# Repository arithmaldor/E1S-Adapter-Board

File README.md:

# Copyright and Disclaimer
Copyright: Jacob Proctor 2018

This documentation describes Open Hardware and is licensed under the
CERN OHL v. 1.2.

You may redistribute and modify this documentation under the terms of the
CERN OHL v.1.2. (http://ohwr.org/cernohl). This documentation is distributed
WITHOUT ANY EXPRESS OR IMPLIED WARRANTY, INCLUDING OF
MERCHANTABILITY, SATISFACTORY QUALITY AND FITNESS FOR A
PARTICULAR PURPOSE. Please see the CERN OHL v.1.2 for applicable
conditions

# SCART to DVI Adapter for Datapath Vision E1S
Lets you connect SCART sources to the DVI input of the Datapath Vision E1S Capture Card.

# BOM
Headphone Port: SJ1-3523N

DVI Port: 74320-9014

Right Angle SCART Plug: https://console5.com/store/female-scart-jp21-through-hole-pcb-mount-21-pin-connector-right-angle.html

Enclosure: Hammond 1591BSBK enclosure

## OSH Park
Find this project on OSh Park: https://www.oshpark.com/shared_projects/juvy79Z5

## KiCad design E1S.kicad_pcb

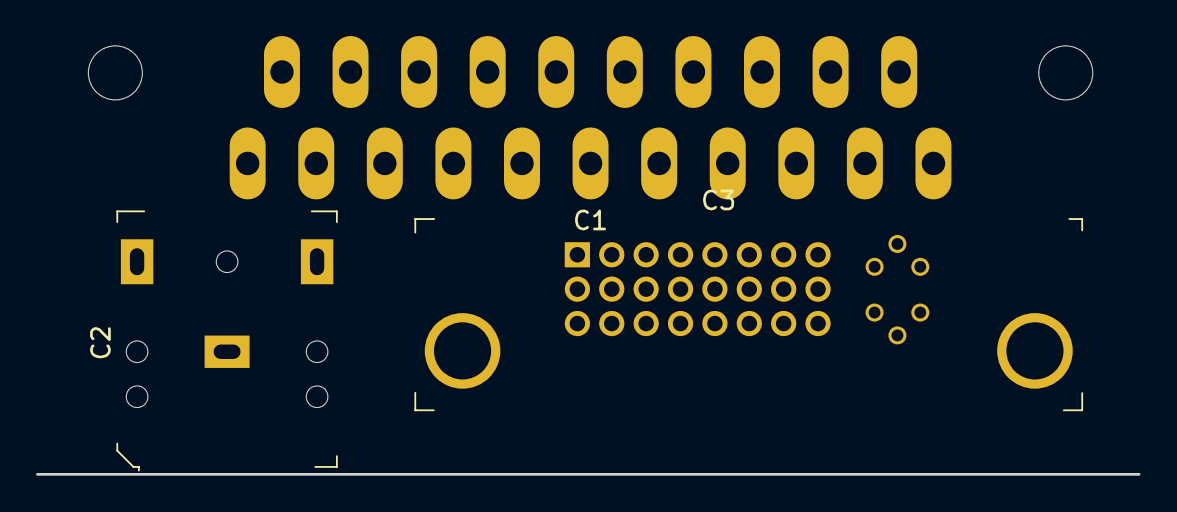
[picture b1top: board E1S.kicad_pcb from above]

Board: 2 copper layers, 3 parts (0 on the bottom side), 8 nets.

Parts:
C1: SCART-F; SCART-Right-Angle
C2: Audio-Jack-3; Headphone_Jack_2.5mm_SJ1-3523N
C3: DVI-I-ANALOG; DVI_Female_74320-9010

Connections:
A_GND: C1.4, C2.1
BLUE: C1.7, C3.C3
GND: C1.5, C1.9, C1.13, C1.17, C1.18, C1.21, C3.C5, C3.SH
GREEN: C1.11, C3.C2
L_AUD: C1.6, C2.2
RED: C1.15, C3.C1
R_AUD: C1.2, C2.3
SYNC: C1.20, C3.C4

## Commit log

2018-06-09 Created Project
2018-06-11 Temp Test Board
    Initial draft of SCART to DVI.
    Do not order, waiting for case to do measurements.
2018-06-19 Final Proto Version
    Designed to fit in Hammond 1591BSBK Enclosure, untested
2018-06-20 tweaks
2018-06-20 Added Readme
2018-06-20 Added OSH Park Link
2018-07-15 shrinking
2018-07-16 attempted fix
2018-07-16 Revert "Merge branch 'master' of https://github.com/arithmaldor/E1S-Adapter-Board"
    This reverts commit 94150dfc6f6b85c60f47e0352986afb0ee45cfad, reversing
    changes made to b5ac63a6ffdfe41caecdf4192571510163740de9.
2018-07-16 reversion
